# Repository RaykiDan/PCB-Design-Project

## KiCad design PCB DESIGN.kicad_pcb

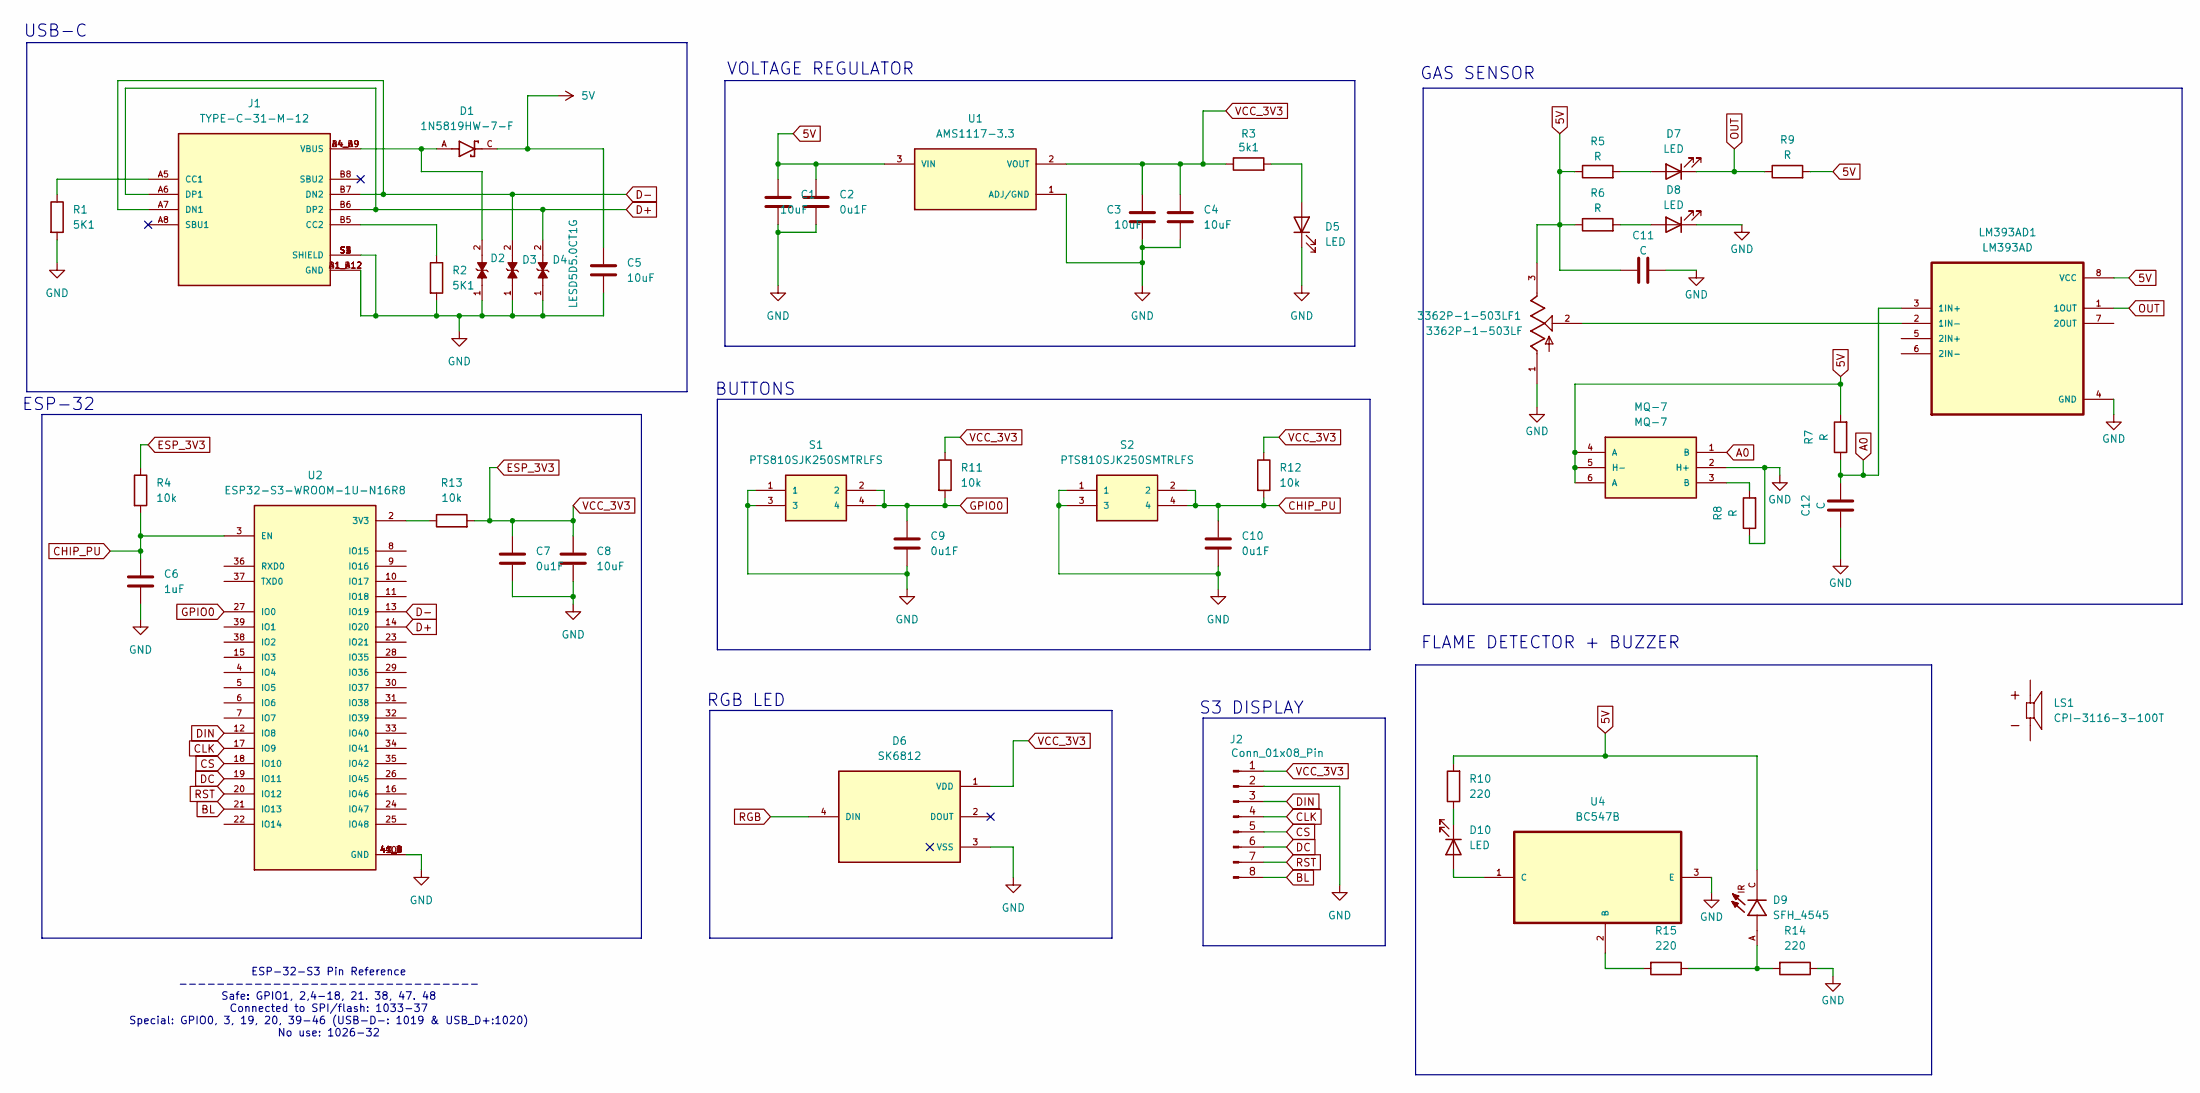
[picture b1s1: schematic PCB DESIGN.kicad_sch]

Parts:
3362P-1-503LF1: 3362P-1-503LF; TRIM_3362P-1-503LF; PARTREV 08/26/10
C1, C3, C4, C5, C8: 10uF; C_0805_2012Metric_Pad1.18x1.45mm_HandSolder
C2, C7, C9, C10: 0u1F; C_0805_2012Metric_Pad1.18x1.45mm_HandSolder
C6: 1uF; C_0805_2012Metric_Pad1.18x1.45mm_HandSolder
C11, C12: C; C_1206_3216Metric_Pad1.33x1.80mm_HandSolder
D1: 1N5819HW-7-F; SOD3715X145N; PARTREV 18-2
D2, D3, D4: LESD5D5.0CT1G; TVS_LESD5D5.0CT1G; PARTREV O
D5: LED; LED_0805_2012Metric
D6: SK6812; LED_SK6812; PARTREV 03
D7, D8, D10: LED; LED_1206_3216Metric_Pad1.42x1.75mm_HandSolder
D9: SFH_4545; DIO_SFH_4545; PARTREV 1.5
J1: TYPE-C-31-M-12; HRO_TYPE-C-31-M-12; PARTREV 2020.12.08
J2: Conn_01x08_Pin; PinHeader_1x08_P2.54mm_Vertical
LM393AD1: LM393AD; SOIC127P599X175-8N
LS1: CPI-3116-3-100T; XDCR_CPI-3116-3-100T; PARTREV 1.0
MQ-7: MQ-7; XDCR_MQ-7; PARTREV N/A
R1, R2: 5K1; R_0805_2012Metric_Pad1.20x1.40mm_HandSolder
R3: 5k1; R_0805_2012Metric_Pad1.20x1.40mm_HandSolder
R4, R11, R12, R13: 10k; R_0805_2012Metric_Pad1.20x1.40mm_HandSolder
R5, R6, R7, R8, R9: R; R_1206_3216Metric_Pad1.30x1.75mm_HandSolder
R10, R14, R15: 220; R_1206_3216Metric_Pad1.30x1.75mm_HandSolder
S1, S2: PTS810SJK250SMTRLFS; PTS810SJG250SMTRLFS; MOUSER_PART_NUMBER 611-PTS810SJK250SMTR
U1: AMS1117-3.3; SOT229P700X180-4N; PARTREV NA
U2: ESP32-S3-WROOM-1U-N16R8; XCVR_ESP32-S3-WROOM-1U-N16R8; PARTREV v1.1
U4: BC547B; TO127P254X732-3; MPN BC547B

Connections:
5V: 3362P-1-503LF1.3, C1.1, C2.1, C5.1, C11.1, D1.C, D9.C, LM393AD1.8 (VCC), MQ-7.4 (A), MQ-7.5 (H-), MQ-7.6 (A), R5.1, R6.1, R7.2, R9.2, R10.2, U1.3 (VIN)
A0: C12.2, LM393AD1.3 (1IN+), MQ-7.1 (B), R7.1
BL: J2.8, U2.21 (IO13)
CHIP_PU: C6.1, C10.1, R4.2, R12.2, S2.2, S2.4, U2.3 (EN)
CLK: J2.4, U2.17 (IO9)
CS: J2.5, U2.18 (IO10)
D+: D4.2, J1.A6 (DP1), J1.B6 (DP2), U2.14 (IO20)
D-: D3.2, J1.A7 (DN1), J1.B7 (DN2), U2.13 (IO19)
DC: J2.6, U2.19 (IO11)
DIN: J2.3, U2.12 (IO8)
GND: 3362P-1-503LF1.1, C1.2, C2.2, C3.2, C4.2, C5.2, C6.2, C7.2, C8.2, C9.2, C10.2, C11.2, C12.1, D2.1, D3.1, D4.1, D5.1 (K), D6.3 (VSS), D8.1 (K), J1.A1_B12 (GND), J1.B1_A12 (GND), J1.S1 (SHIELD), J1.S2 (SHIELD), J1.S3 (SHIELD), J1.S4 (SHIELD), J2.2, LM393AD1.4 (GND), MQ-7.2 (H+), R1.2, R2.2, R8.1, R14.1, S1.1, S1.3, S2.1, S2.3, U1.1 (ADJ/GND), U2.1 (GND), U2.40 (GND), U2.41_1 (GND), U2.41_2 (GND), U2.41_3 (GND), U2.41_4 (GND), U2.41_5 (GND), U2.41_6 (GND), U2.41_7 (GND), U2.41_8 (GND), U2.41_9 (GND), U4.3 (E)
GPIO0: C9.1, R11.2, S1.2, S1.4, U2.27 (IO0)
unnamed: D1.A, D2.2, J1.A4_B9 (VBUS), J1.B4_A9 (VBUS)
unnamed: D5.2 (A), R3.2
unnamed: D7.2 (A), R5.2
unnamed: D8.2 (A), R6.2
unnamed: D9.A, R14.2, R15.1
unnamed: D10.2 (A), U4.1 (C)
unnamed: D10.1 (K), R10.1
unnamed: J1.A5 (CC1), R1.1
unnamed: J1.B5 (CC2), R2.1
unnamed: 3362P-1-503LF1.2, LM393AD1.2 (1IN-)
unnamed: MQ-7.3 (B), R8.2
unnamed: R13.1, U2.2 (3V3)
unnamed: R15.2, U4.2 (B)
OUT: D7.1 (K), LM393AD1.1 (1OUT), R9.1
RGB: D6.4 (DIN)
RST: J2.7, U2.20 (IO12)

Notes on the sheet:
FLAME DETECTOR + BUZZER
ESP-32
S3 DISPLAY
RGB LED
ESP-32-S3 Pin Reference -------------------------------- Safe: GPIO1, 2,4-18, 21. 38, 47. 48 Connected to SPI/flash: 1033-37 Special: GPIO0, 3, 19, 20, 39-46 (USB-D-: 1019 & USB_D+:1020) No use: 1026-32
USB-C
VOLTAGE REGULATOR
GAS SENSOR
BUTTONS

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
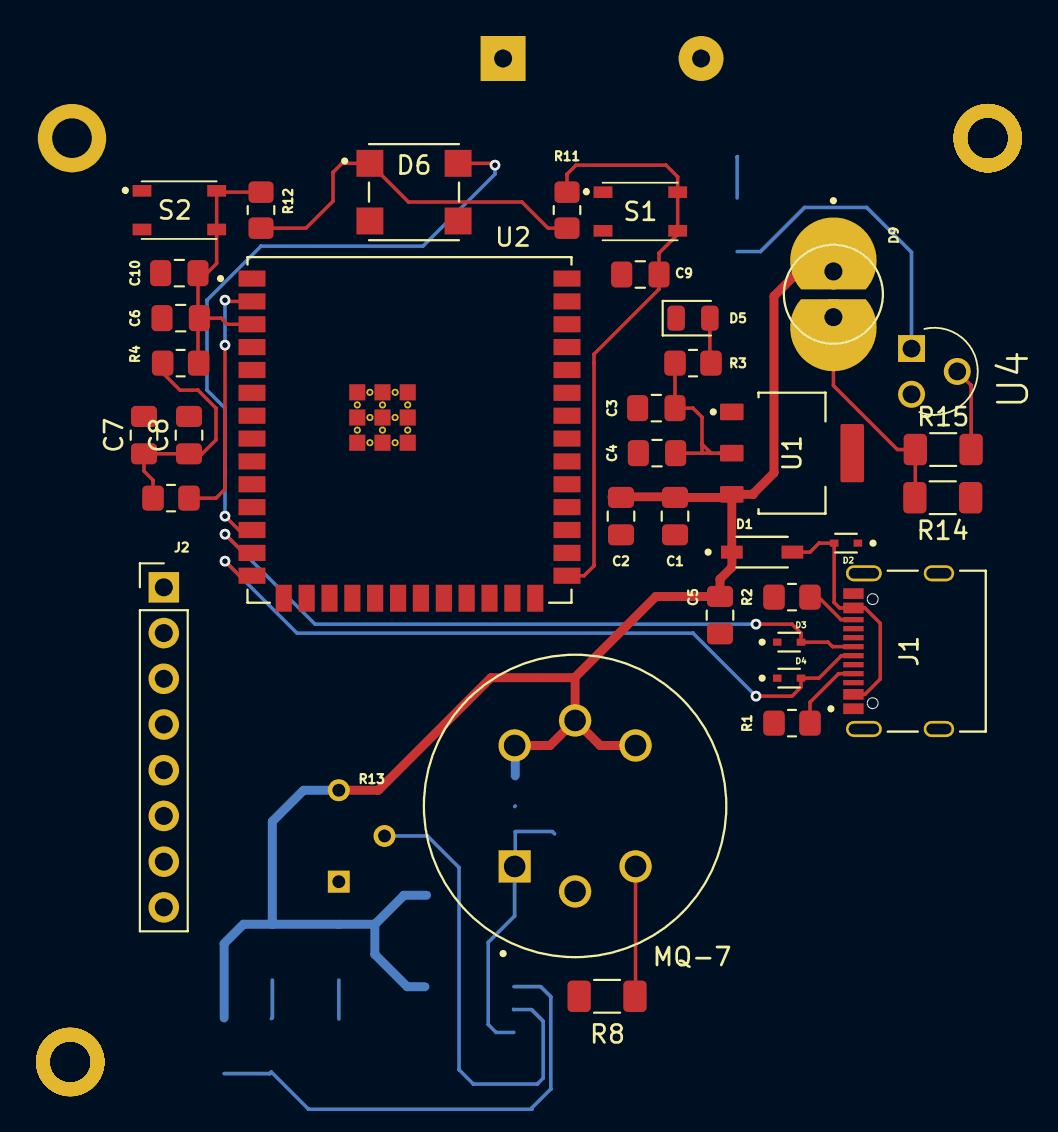
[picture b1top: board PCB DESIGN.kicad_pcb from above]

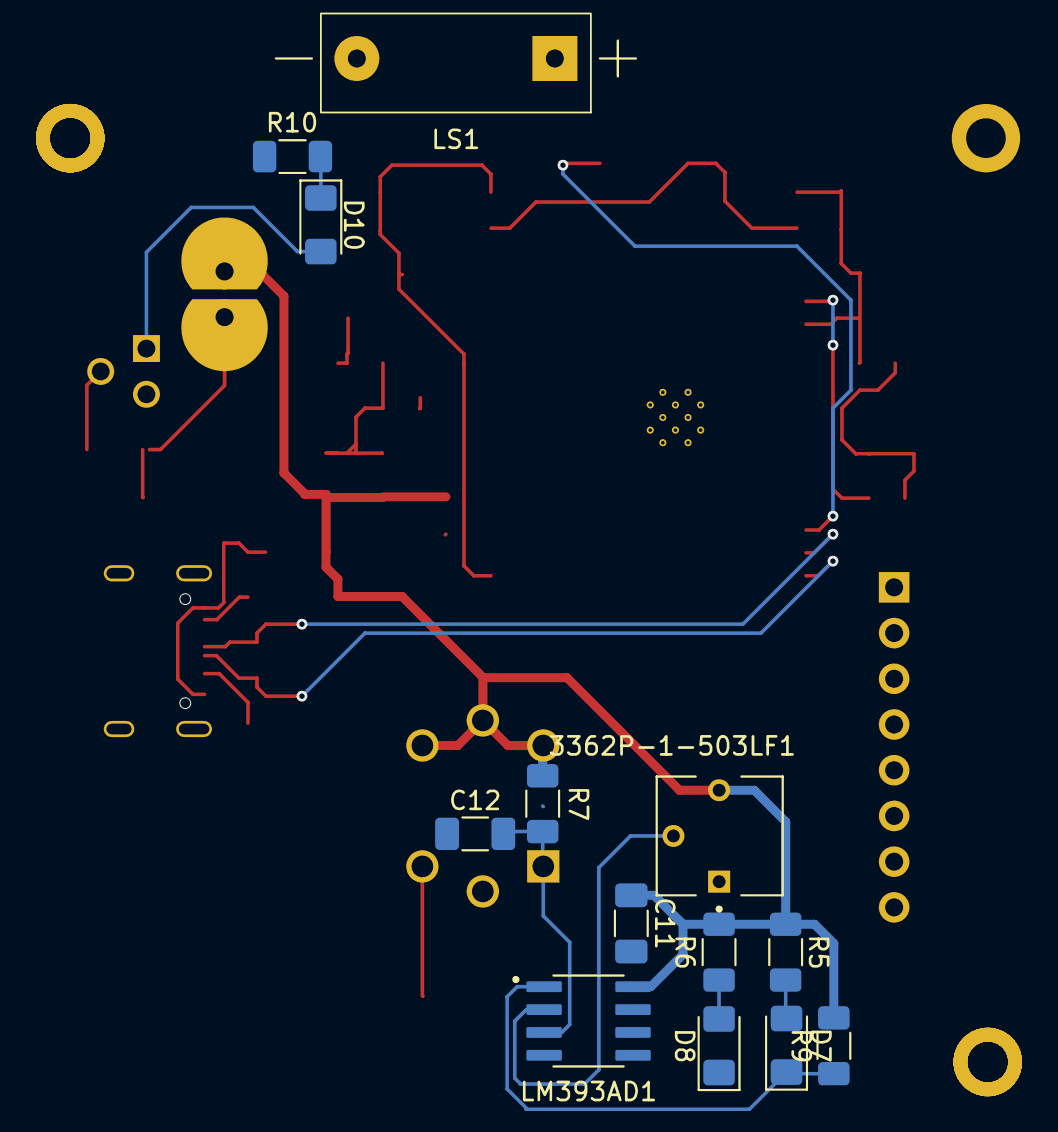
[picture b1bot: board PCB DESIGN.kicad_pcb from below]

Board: 2 copper layers, 48 parts (13 on the bottom side), 29 nets.

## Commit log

2025-05-29 gas detection feature
2025-05-29 nambahin footprint
2025-05-29 footprint placement + schematic repair
